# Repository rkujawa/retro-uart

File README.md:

# retro-uart
Retro-fitting 16C750E into DIP socket! For all your retro hardware project needs.

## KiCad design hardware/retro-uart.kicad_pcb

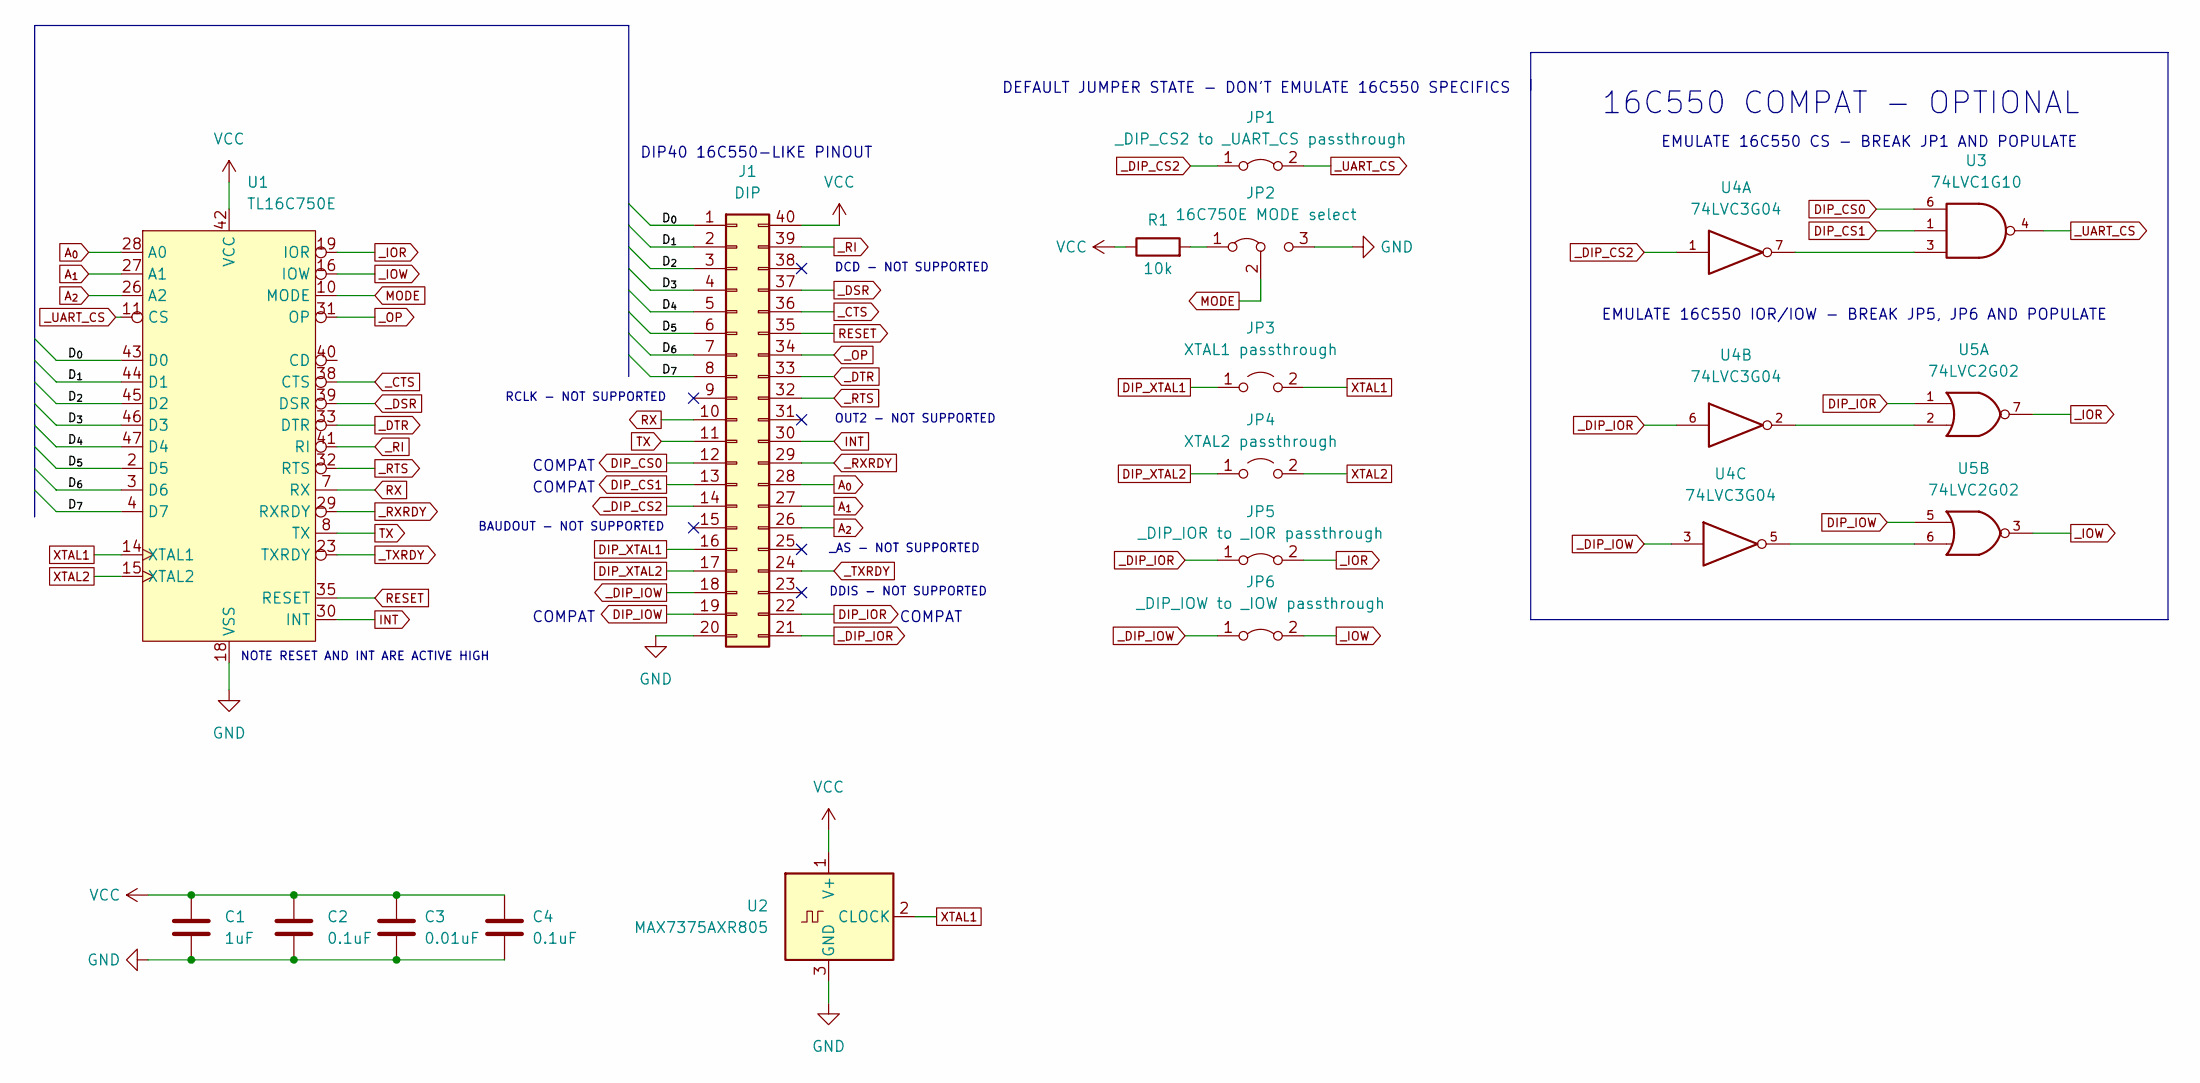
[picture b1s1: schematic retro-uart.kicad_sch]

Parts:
C1: 1uF; C_0603_1608Metric_Pad1.08x0.95mm_HandSolder
C2, C4: 0.1uF; C_0603_1608Metric_Pad1.08x0.95mm_HandSolder
C3: 0.01uF; C_0603_1608Metric_Pad1.08x0.95mm_HandSolder
J1: DIP; DIP-40_W15.24mm
JP1: _DIP_CS2 to _UART_CS passthrough; SolderJumper-2_P1.3mm_Bridged_Pad1.0x1.5mm
JP2: 16C750E MODE select; SolderJumper-3_P1.3mm_Bridged12_Pad1.0x1.5mm_NumberLabels
JP3: XTAL1 passthrough; SolderJumper-2_P1.3mm_Open_Pad1.0x1.5mm
JP4: XTAL2 passthrough; SolderJumper-2_P1.3mm_Open_Pad1.0x1.5mm
JP5: _DIP_IOR to _IOR passthrough; SolderJumper-2_P1.3mm_Bridged_Pad1.0x1.5mm
JP6: _DIP_IOW to _IOW passthrough; SolderJumper-2_P1.3mm_Bridged_Pad1.0x1.5mm
R1: 10k; R_0603_1608Metric_Pad0.98x0.95mm_HandSolder
U1: TL16C750E; TQFP-48_7x7mm_P0.5mm
U2: MAX7375AXR805; SOT-323_SC-70
U3: 74LVC1G10; SOT-363_SC-70-6_Handsoldering
U4: 74LVC3G04; TSSOP-8_3x3mm_P0.65mm
U5: 74LVC2G02; TSSOP-8_3x3mm_P0.65mm

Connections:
/D_{0}: J1.1, U1.43 (D0)
/D_{1}: J1.2, U1.44 (D1)
/D_{2}: J1.3, U1.45 (D2)
/D_{3}: J1.4, U1.46 (D3)
/D_{4}: J1.5, U1.47 (D4)
/D_{5}: J1.6, U1.2 (D5)
/D_{6}: J1.7, U1.3 (D6)
/D_{7}: J1.8, U1.4 (D7)
A_{0}: J1.28, U1.28 (A0)
A_{1}: J1.27, U1.27 (A1)
A_{2}: J1.26, U1.26 (A2)
DIP_CS0: J1.12, U3.6
DIP_CS1: J1.13, U3.1
DIP_IOR: J1.22, U5.1
DIP_IOW: J1.19, U5.5
DIP_XTAL1: J1.16, JP3.1 (A)
DIP_XTAL2: J1.17, JP4.1 (A)
GND: C1.2, C2.2, C3.2, C4.2, J1.20, JP2.3 (B), U1.18 (VSS), U2.3 (GND), U3.2 (GND), U4.4 (GND), U5.4 (GND)
INT: J1.30, U1.30 (INT)
MODE: JP2.2 (C), U1.10 (MODE)
unnamed: JP2.1 (A), R1.2
unnamed: U3.3, U4.7
unnamed: U4.2, U5.2
unnamed: U4.5, U5.6
RESET: J1.35, U1.35 (RESET)
RX: J1.10, U1.7 (RX)
TX: J1.11, U1.8 (TX)
VCC: C1.1, C2.1, C3.1, C4.1, J1.40, R1.1, U1.42 (VCC), U2.1 (V+), U3.5 (VCC), U4.8 (VCC), U5.8 (VCC)
XTAL1: JP3.2 (B), U1.14 (XTAL1), U2.2 (CLOCK)
XTAL2: JP4.2 (B), U1.15 (XTAL2)
_CTS: J1.36, U1.38 (CTS)
_DIP_CS2: J1.14, JP1.1 (A), U4.1
_DIP_IOR: J1.21, JP5.1 (A), U4.6
_DIP_IOW: J1.18, JP6.1 (A), U4.3
_DSR: J1.37, U1.39 (DSR)
_DTR: J1.33, U1.33 (DTR)
_IOR: JP5.2 (B), U1.19 (IOR), U5.7
_IOW: JP6.2 (B), U1.16 (IOW), U5.3
_OP: J1.34, U1.31 (OP)
_RI: J1.39, U1.41 (RI)
_RTS: J1.32, U1.32 (RTS)
_RXRDY: J1.29, U1.29 (RXRDY)
_TXRDY: J1.24, U1.23 (TXRDY)
_UART_CS: JP1.2 (B), U1.11 (CS), U3.4

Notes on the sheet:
DDIS - NOT SUPPORTED
EMULATE 16C550 CS - BREAK JP1 AND POPULATE
COMPAT
_AS - NOT SUPPORTED
DCD - NOT SUPPORTED
NOTE RESET AND INT ARE ACTIVE HIGH
16C550 COMPAT - OPTIONAL
DEFAULT JUMPER STATE - DON'T EMULATE 16C550 SPECIFICS
BAUDOUT - NOT SUPPORTED
OUT2 - NOT SUPPORTED
RCLK - NOT SUPPORTED
DIP40 16C550-LIKE PINOUT
EMULATE 16C550 IOR/IOW - BREAK JP5, JP6 AND POPULATE

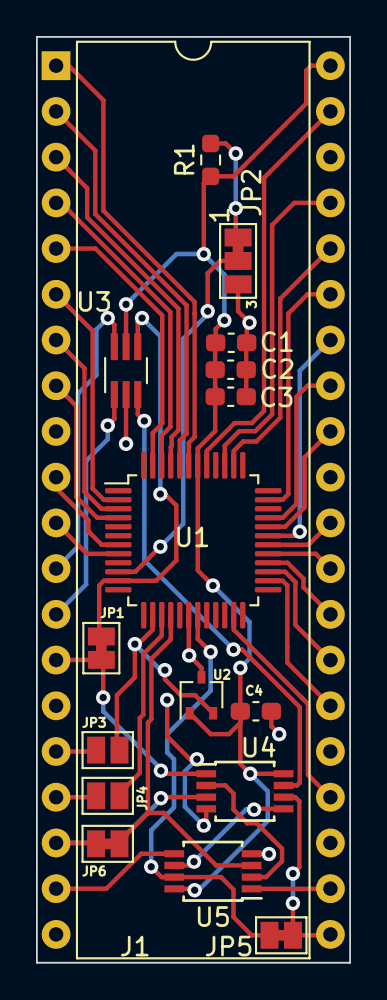
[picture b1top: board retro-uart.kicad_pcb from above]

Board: 2 copper layers, 17.4 x 51.4 mm, 17 parts (0 on the bottom side), 44 nets.

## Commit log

2023-01-22 Initial import of KiCad schematics and PCB.
2023-01-22 Fix courtyard issues.
